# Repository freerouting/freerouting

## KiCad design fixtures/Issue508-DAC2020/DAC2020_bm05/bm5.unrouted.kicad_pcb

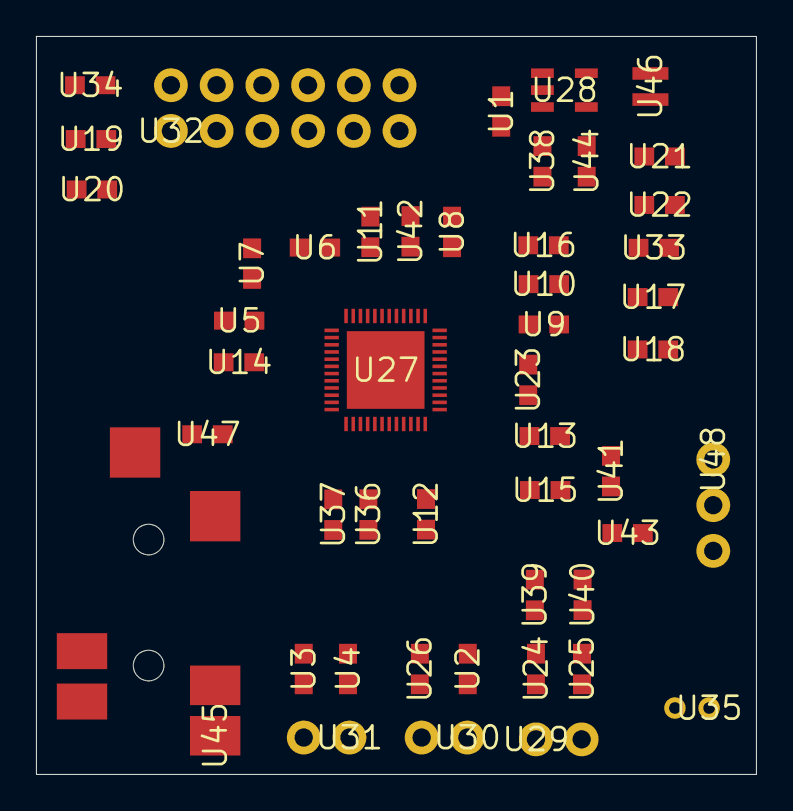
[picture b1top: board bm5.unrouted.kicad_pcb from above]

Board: 2 copper layers, 40.0 x 41.0 mm, 48 parts (0 on the bottom side), 47 nets, no tracks yet.

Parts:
U1, U2, U3, U4, U5, U6, U7, U8, U9, U10, U11, U12, U13, U14, U15, U16, U17, U18, U19, U20, U21, U22, U23, U24, U25, U26, U33, U34, U36, U37, U38, U39, U40, U41, U42, U43, U44, U47: 0603
U27: QFN50P700X700X100-49N
U28: SOT95P284X122-5N
U29, U30, U31: 1X02
U32: 2X6
U35: CMC-2242PBL-A
U45: SJ-43514-SMT-TR
U46: NRH2412T2R2MNGH
U48: 1X03

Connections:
3.3V: U32.2, U34.2
5V: U1.2, U28.1, U32.12, U33.2, U38.1
/1.8VDD: U21.1, U22.1, U27.7, U27.13, U27.21, U28.4, U46.2
/3.3VDD: U19.1, U20.1, U27.29, U34.1, U36.1, U37.1, U48.1
/CPVREF: U27.17, U42.1
/HPOL: U27.18, U45.2, U47.1
/HPOR: U27.19, U45.3
/IN1P: U23.1, U27.4, U41.2, U45.1
/IN2P: U16.1, U35.2, U43.2, U48.3
/LOUTL: U27.11, U39.1
/LOUTR: U27.12, U40.1
/MICBIAS1: U15.2, U27.2, U41.1, U43.1
/SPKVDD: U17.1, U18.1, U27.44, U27.48, U33.1
/SPOLN: U26.1, U27.47, U30.2
/SPOLP: U2.1, U27.1, U30.1
/SPORN: U3.1, U27.43, U31.2
/SPORP: U4.1, U27.45, U31.1
/XADUIO_I2S0_BCLK: U27.37, U32.5
/XADUIO_I2S0_LRCKL: U27.36, U32.1
/XADUIO_SCL: U27.39, U32.7, U37.2
/XAUDIO_I2S0_DIN: U27.35, U32.4
/XAUDIO_I2S0_DOUT: U27.34, U32.3
/XAUDIO_I2S0_MCLK: U27.38, U32.6
/XAUDIO_IRQ: U27.41, U32.10
/XAUDIO_SDA: U27.40, U32.8, U36.2
GND: U1.1, U2.2, U3.2, U4.2, U5.2, U8.1, U9.1, U10.1, U11.2, U12.1, U13.1, U14.1, U15.1, U17.2, U18.2, U19.2, U20.2, U21.2, U22.2, U26.2, U27.5, U27.15, U27.16, U27.22, U27.49, U28.2, U32.11, U35.1, U42.2, U44.1, U45.4, U48.2
unnamed: U11.1, U27.20
unnamed: U23.2, U27.6
unnamed: U24.1, U39.2
unnamed: U24.2, U29.1
unnamed: U25.1, U40.2
unnamed: U25.2, U29.2
unnamed: U5.1, U27.27
unnamed: U6.1, U27.24
unnamed: U6.2, U27.23
unnamed: U7.1, U27.25
unnamed: U7.2, U27.26
unnamed: U8.2, U27.14
unnamed: U9.2, U27.8
unnamed: U10.2, U27.9
unnamed: U12.2, U27.46
unnamed: U13.2, U27.3
unnamed: U14.2, U27.28
unnamed: U16.2, U27.10
unnamed: U28.3, U38.2, U44.2
unnamed: U28.5, U46.1
unnamed: U45.5, U47.2

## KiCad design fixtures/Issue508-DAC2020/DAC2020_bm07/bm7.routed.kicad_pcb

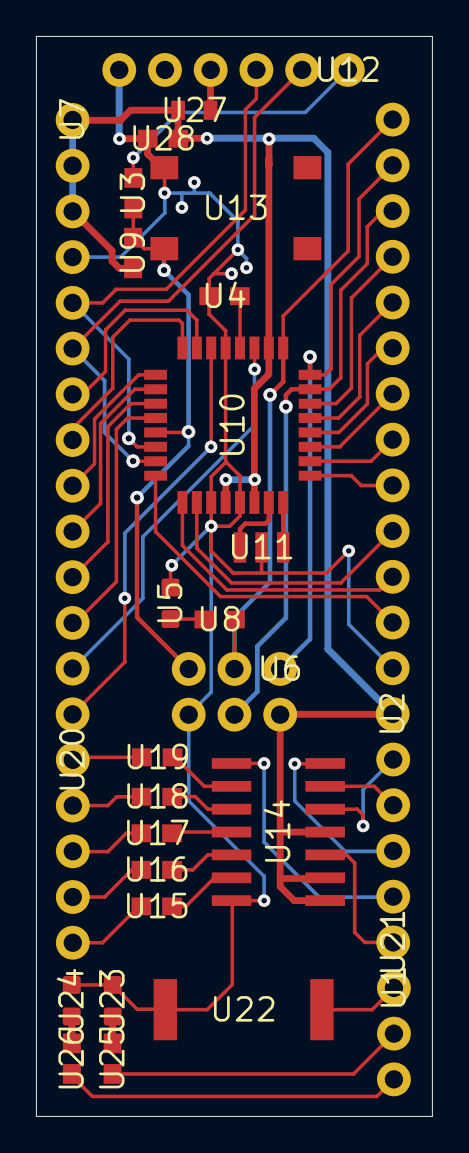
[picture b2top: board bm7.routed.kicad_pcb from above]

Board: 2 copper layers, 22.0 x 60.0 mm, 28 parts (0 on the bottom side), 51 nets.

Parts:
U1: 1X03
U2, U7: 1X14
U3, U4, U8, U9, U15, U16, U17, U18, U19, U25, U26, U28: 0603
U5, U23, U24: LED-0603
U6: 2X3
U10: TQFP32-08
U11: RESONATOR-SMD
U12: FTDI_BASIC
U13: TACTILE_SWITCH_SMD_6.2MM_TALL
U14: SO14
U20, U21: 1X05
U22: PKMCS
U27: FUSC1608X100N

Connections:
/A0: U7.7, U10.23
/A1: U7.8, U10.24
/A2: U7.9, U10.25
/A3: U7.10, U10.26
/A4: U7.11, U10.27
/A5: U7.12, U10.28
/A6: U7.13, U10.19
/A7: U7.14, U10.22
/D2: U2.3, U10.32
/D3: U2.4, U10.1
/D4: U2.5, U10.2
/D5: U2.6, U10.9
/D6: U2.7, U10.10
/D7: U2.8, U10.11
/D8: U2.9, U10.12
/D9: U2.10, U10.13
/D10: U2.11, U10.14
/DTR: U3.1, U12.DTR
/GO: U14.3, U21.1
/MISO: U2.13, U6.1, U10.16
/MOSI: U2.12, U6.4, U10.15
/OUT1: U14.8, U21.2
/OUT2: U14.7, U21.3
/OUT3: U14.6, U21.4
/OUT4: U14.5, U21.5
/RST: U3.2, U6.5, U9.1, U10.29, U13.B2
/RXI: U7.5, U10.30, U12.TXO
/SCK: U2.14, U6.3, U8.1, U10.17
/TXO: U7.6, U10.31, U12.RXI
GND: U2.2, U4.2, U5.C, U6.6, U7.4, U10.3, U10.5, U10.21, U11.2, U12.GND, U13.A2, U14.14, U22.1, U23.C, U24.C, U28.2
unnamed: U4.1, U10.20
unnamed: U5.A, U8.2
unnamed: U23.A, U25.1
unnamed: U24.A, U26.1
unnamed: U12.VCC, U27.1
unnamed: U14.9, U19.2
unnamed: U14.10, U18.2
unnamed: U14.11, U17.2
unnamed: U14.12, U16.2
unnamed: U14.13, U15.2
unnamed: U19.1, U20.1
unnamed: U18.1, U20.2
unnamed: U17.1, U20.3
unnamed: U16.1, U20.4
unnamed: U15.1, U20.5
unnamed: U1.1, U22.2
unnamed: U1.2, U25.2
unnamed: U1.3, U26.2
unnamed: U10.7, U11.3
unnamed: U10.8, U11.1
VCC: U2.1, U6.2, U7.1, U7.2, U7.3, U9.2, U10.4, U10.6, U10.18, U14.1, U14.2, U14.4, U27.2, U28.1

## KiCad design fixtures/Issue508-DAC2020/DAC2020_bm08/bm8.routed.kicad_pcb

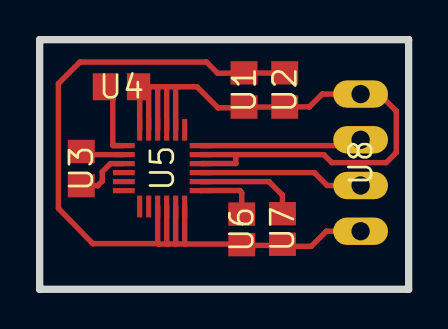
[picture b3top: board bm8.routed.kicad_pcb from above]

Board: 2 copper layers, 20.5 x 13.9 mm, 8 parts (0 on the bottom side), 9 nets.

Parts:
U1, U2, U3, U4: C0805
U5: LGA-24
U6, U7: R0805
U8: MA04-1

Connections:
/SCL: U5.21, U8.2
/SDA: U5.24, U8.3
GND: U1.2, U2.2, U4.1, U5.2, U5.3, U5.4, U5.5, U5.6, U5.22, U5.23, U8.4
unnamed: U3.1, U5.9
unnamed: U3.2, U5.8
unnamed: U4.2, U5.7
unnamed: U5.19, U6.1
unnamed: U5.20, U7.1
VDD: U1.1, U2.1, U5.15, U5.16, U5.17, U5.18, U6.2, U7.2, U8.1

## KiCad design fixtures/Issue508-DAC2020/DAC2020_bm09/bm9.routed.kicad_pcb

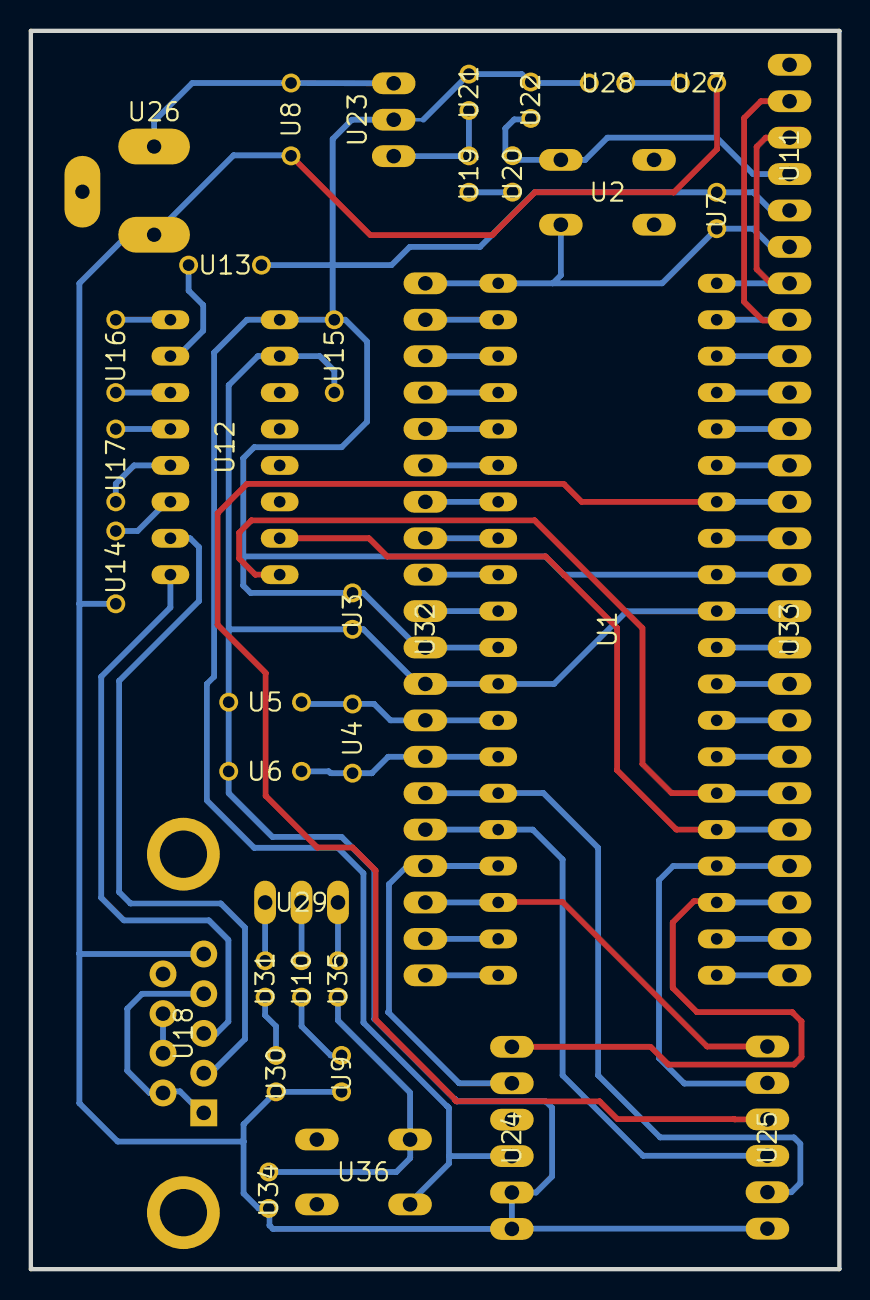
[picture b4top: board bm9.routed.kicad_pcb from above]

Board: 16 copper layers, 56.4 x 86.4 mm, 36 parts (0 on the bottom side), 58 nets.

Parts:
U1: DIL40
U2, U36: B3F-10XX
U3, U22: C025-024X044
U4: HC49_S
U5, U6, U13, U14, U15, U16, U17: C050-024X044
U7, U10, U19, U20, U21, U28, U31, U34, U35: V526-0
U8: C050-025X075
U9, U27, U30: LED3MM
U11, U24, U25: 1X06
U12: DIL16
U18: DB9
U23: 317TS
U26: 733980-62
U29: MA03-1
U32, U33: MA20-1

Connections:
/3.3V_SRC: U1.11, U1.32, U3.1, U7.1, U11.2, U12.16, U13.2, U15.1, U21.2, U22.1, U23.2, U24.3, U28.1, U32.10, U33.9, U36.1
/MRF_CS: U1.17, U24.5, U32.4
/MRF_INT: U1.34, U25.3, U33.7
/MRF_RESET: U1.15, U25.5, U32.6
/MRF_SCK: U1.18, U25.1, U32.3
/MRF_SDI: U1.23, U24.6, U33.18
/MRF_SDO: U1.24, U25.2, U33.17
/MRF_WAKE: U1.16, U25.4, U32.5
/N$17: U1.26, U12.9, U33.15
/N$21: U1.25, U12.10, U33.16
/OS1: U1.13, U4.1, U5.1, U32.8
/OSC2: U1.14, U4.2, U6.1, U32.7
GND: U1.12, U1.31, U2.1, U3.2, U5.2, U6.2, U8.2, U9.K, U11.3, U12.15, U14.1, U15.2, U18.5, U20.1, U22.2, U24.1, U24.2, U25.6, U26.1, U27.K, U30.K, U32.9, U33.10, U34.2
unnamed: U12.2, U13.1
unnamed: U12.6, U14.2
unnamed: U12.1, U16.1
unnamed: U12.3, U16.2
unnamed: U12.4, U17.1
unnamed: U12.5, U17.2
unnamed: U8.1, U23.3, U26.2
unnamed: U12.7, U18.2
unnamed: U12.8, U18.3
unnamed: U1.1, U2.3, U7.2, U11.1, U32.20
unnamed: U1.2, U32.19
unnamed: U1.3, U32.18
unnamed: U1.4, U32.17
unnamed: U1.5, U32.16
unnamed: U1.6, U32.15
unnamed: U1.7, U32.14
unnamed: U1.8, U32.13
unnamed: U1.9, U32.12
unnamed: U1.10, U32.11
unnamed: U1.19, U32.2
unnamed: U1.20, U32.1
unnamed: U1.21, U33.20
unnamed: U1.22, U33.19
unnamed: U1.27, U33.14
unnamed: U1.28, U33.13
unnamed: U1.29, U33.12
unnamed: U1.30, U33.11
unnamed: U1.33, U33.8
unnamed: U1.35, U33.6
unnamed: U1.36, U33.5
unnamed: U1.37, U33.4
unnamed: U1.38, U33.3
unnamed: U1.39, U11.5, U33.2
unnamed: U1.40, U11.4, U33.1
unnamed: U19.2, U21.1, U23.1
unnamed: U27.A, U28.2
unnamed: U30.A, U31.2
unnamed: U9.A, U10.2
unnamed: U34.1, U35.2, U36.3
unnamed: U29.3, U35.1
unnamed: U10.1, U29.2
unnamed: U29.1, U31.1
unnamed: U19.1, U20.2
unnamed: U18.1, U18.4, U18.6
unnamed: U18.7, U18.8

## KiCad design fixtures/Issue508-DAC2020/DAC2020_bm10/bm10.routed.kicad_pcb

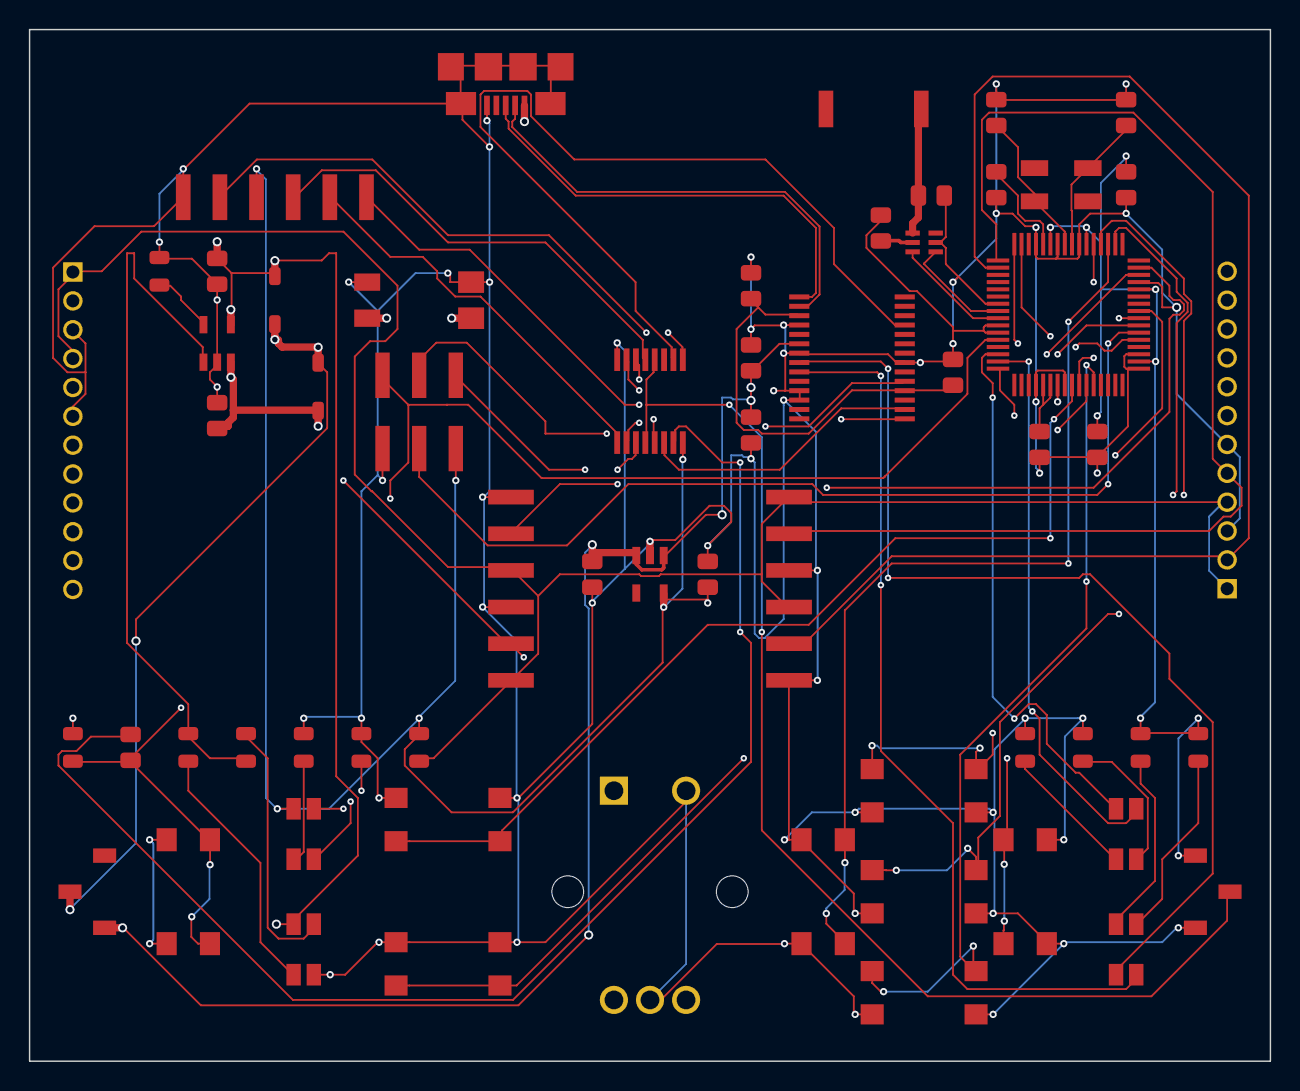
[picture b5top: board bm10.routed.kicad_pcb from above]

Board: 4 copper layers, 86.0 x 71.5 mm, 61 parts (0 on the bottom side), 63 nets.

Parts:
A1: ANTENNA-CHIP; ANT-2.4GHZ-6.5X2.2MM
B1, B4, B5, B6, B7, B8, B9, B10: PUSHBUTTON_-4.5X4.5; 4.5MM_TACTILE_SWITCH_TL3305AF160QG
B2: BALUN0805; BALUN
B3: BATTERY-SPRING-SMD; WIRE-TERMINAL-1X2-2.5MM-SMD-AVX-009276002021106
C1, C8, C9: 0.1uF; CAPC2012X140_HS
C2: 0.75pF; CAPC2012X140_HS
C3: 22pF; CAPC2012X140_HS
C4, C10, C11, C12, C13, C16, C17: 1uF; CAPC2012X140_HS
C5, C6, C7: 10uF; CAPC2012X140_HS
C14, C15: 12pF; CAPC2012X140_HS
D1, D4, D5, D6: LED-2X-GREEN_RED; LED-2X-LTST-C155
D2, D3: 360mV; SOD3716X135_HS
E1: ROTARY-ENCODER-W_BUTTON-BOURNS-PEC12R-4217F; BOURNS-PEC12R
J1: USB-MICROA-AMPHENOL-10118192-0001LF; USB-MICROA-10118192-0001LF
J2, J3: 2.4K; JST-13-PTH
J4: AVR_SPI_PRG_6-SMD; 2X3-SMD
J7, J8: FRSKY-GIMBAL-2X-SERVO-SMD; 2X-SERVO-SMD
JP1: FTDI_BASIC-SMD; FTDI-BASIC-SMD
R1, R3, R13, R14, R15, R16, R17, R18: 510; RESC2012X60_HS
R2: 10K; RESC2012X60_HS
R7: 2.2K; RESC2012X60_HS
R8: 1.2K; RESC2012X60_HS
S1, S2: POWER-SWITCH-MFS201N-9-Z-SMD-VERTICAL; JS102011JCQN
U1: 3.3V; SOT23-DBV
U2: MCP73831T-2ACI/OT; SOT23-5
U3: FT232RLSSOP; SSOP28DB
U4: ATMEGA128RFA1; QFN-64
U5: DPDT-X2; SOP65P640X110-16
Y1: CRYSTAL5X3; CRYSTAL-SMD-5X3

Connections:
3V3: C12.1, C16.1, C17.1, D4.A2, J4.2, JP1.VCC, R2.2, R8.2, R13.2, R14.2, S2.1, U1.5, U4.23, U4.34, U4.44, U4.54, U4.59, U5.16
/BTN1/SCL: B4.3, B4.4, U4.25
/BTN2/SDA: B5.3, B5.4, U4.26
/BTN_CENTER: B9.1, B9.2, U4.53
/BTN_DOWN: B10.1, B10.2, U4.28
/BTN_LEFT: B7.1, B7.2, U4.51
/BTN_RIGHT: B8.1, B8.2, U4.52
/BTN_UP: B6.1, B6.2, U4.50
/CTS: U3.11, U5.2
/CTS-1: JP1.CTS, U5.1
/DTR: U3.2, U5.14
/DTR-0: C1.2, U5.15
/DTR-1: JP1.DTR, U5.13
/E1-A: E1.A, U4.40
/E1-B: E1.B, U4.41
/E1-BUT: E1.BUTA, U4.27
/FTDI_OUT: C4.2, C9.1, U3.4, U3.17
/GREF: J2.1, J2.4, J3.1, J3.4, J7.1, J7.4, J8.1, J8.4, R8.1
/MISO: J4.1, U4.39
/MOSI: J4.4, U4.38
/PITCH: J3.V, J8.V, U4.2
/RESET: B1.1, B1.2, C1.1, J4.5, R2.1, U4.12
/RF: D4.A1, U4.16
/ROLL: J3.H, J8.H, U4.1
/RXI: U3.5, U5.10
/RXI-0: U4.47, U5.11
/RXI-1: JP1.RXI, U5.9
/RXLED: D5.C2, U3.22
/SCK: J4.3, U4.37
/THROTTLE: J2.V, J7.V, U4.64
/TXLED: D5.C1, U3.23
/TXO: U3.1, U5.6
/TXO-0: U4.46, U5.7
/TXO-1: JP1.TXO, U5.5
/USB_D_N: J1.2, U3.16
/USB_D_P: J1.3, U3.15
/VBUS: C5.1, D1.A2, D2.A, J1.1, U2.4
/VREG_IN: C7.1, C8.1, C10.1, S1.1, U1.1, U1.3, U3.20
/YAW: J2.H, J7.H, U4.63
GND: B1.3, B1.4, B2.5, B3.2A, B3.2B, B4.1, B4.2, B5.1, B5.2, B6.3, B6.4, B7.3, B7.4, B8.3, B8.4, B9.3, B9.4, B10.3, B10.4, C2.2, C3.1, C4.1, C5.2, C6.2, C7.2, C8.2, C9.2, C10.2, C11.2, C12.2, C13.2, C14.2, C15.2, C16.2, C17.2, D1.C1, E1.BUTB, E1.C, J1.5, J1.6, J1.7, J1.8, J1.9, J1.10, J1.11, J2.3, J2.6, J3.3, J3.6, J4.6, J7.3, J7.6, J8.3, J8.6, JP1.GND, R7.2, R15.1, R16.1, R17.1, R18.1, S2.3, U1.2, U2.2, U3.7, U3.18, U3.21, U3.25, U3.26, U4.7, U4.10, U4.11, U4.20, U4.24, U4.33, U4.35, U4.45, U4.55, U4.58, U4.61, U5.8
unnamed: A1.FEED, B2.1, C2.1
unnamed: B2.2, C3.2
unnamed: B2.3, U4.9
unnamed: B2.4, U4.8
unnamed: B3.1A, B3.1B, C6.1, D3.A, U2.3
unnamed: C11.1, U4.21, U4.22
unnamed: C13.1, U4.60
unnamed: C14.1, U4.57, Y1.3
unnamed: C15.1, U4.56, Y1.1
unnamed: D1.A1, R3.1
unnamed: D1.C2, R1.1
unnamed: D4.C1, R15.2
unnamed: D4.C2, R16.2
unnamed: D5.A1, R14.1
unnamed: D5.A2, R13.1
unnamed: D6.A1, U4.15
unnamed: D6.A2, U4.14
unnamed: D6.C1, R18.2
unnamed: D6.C2, R17.2
unnamed: R1.2, R3.2, U2.1
unnamed: R7.1, U2.5
unnamed: S2.2, U5.4, U5.12
VBAT: D2.C, D3.C, S1.2

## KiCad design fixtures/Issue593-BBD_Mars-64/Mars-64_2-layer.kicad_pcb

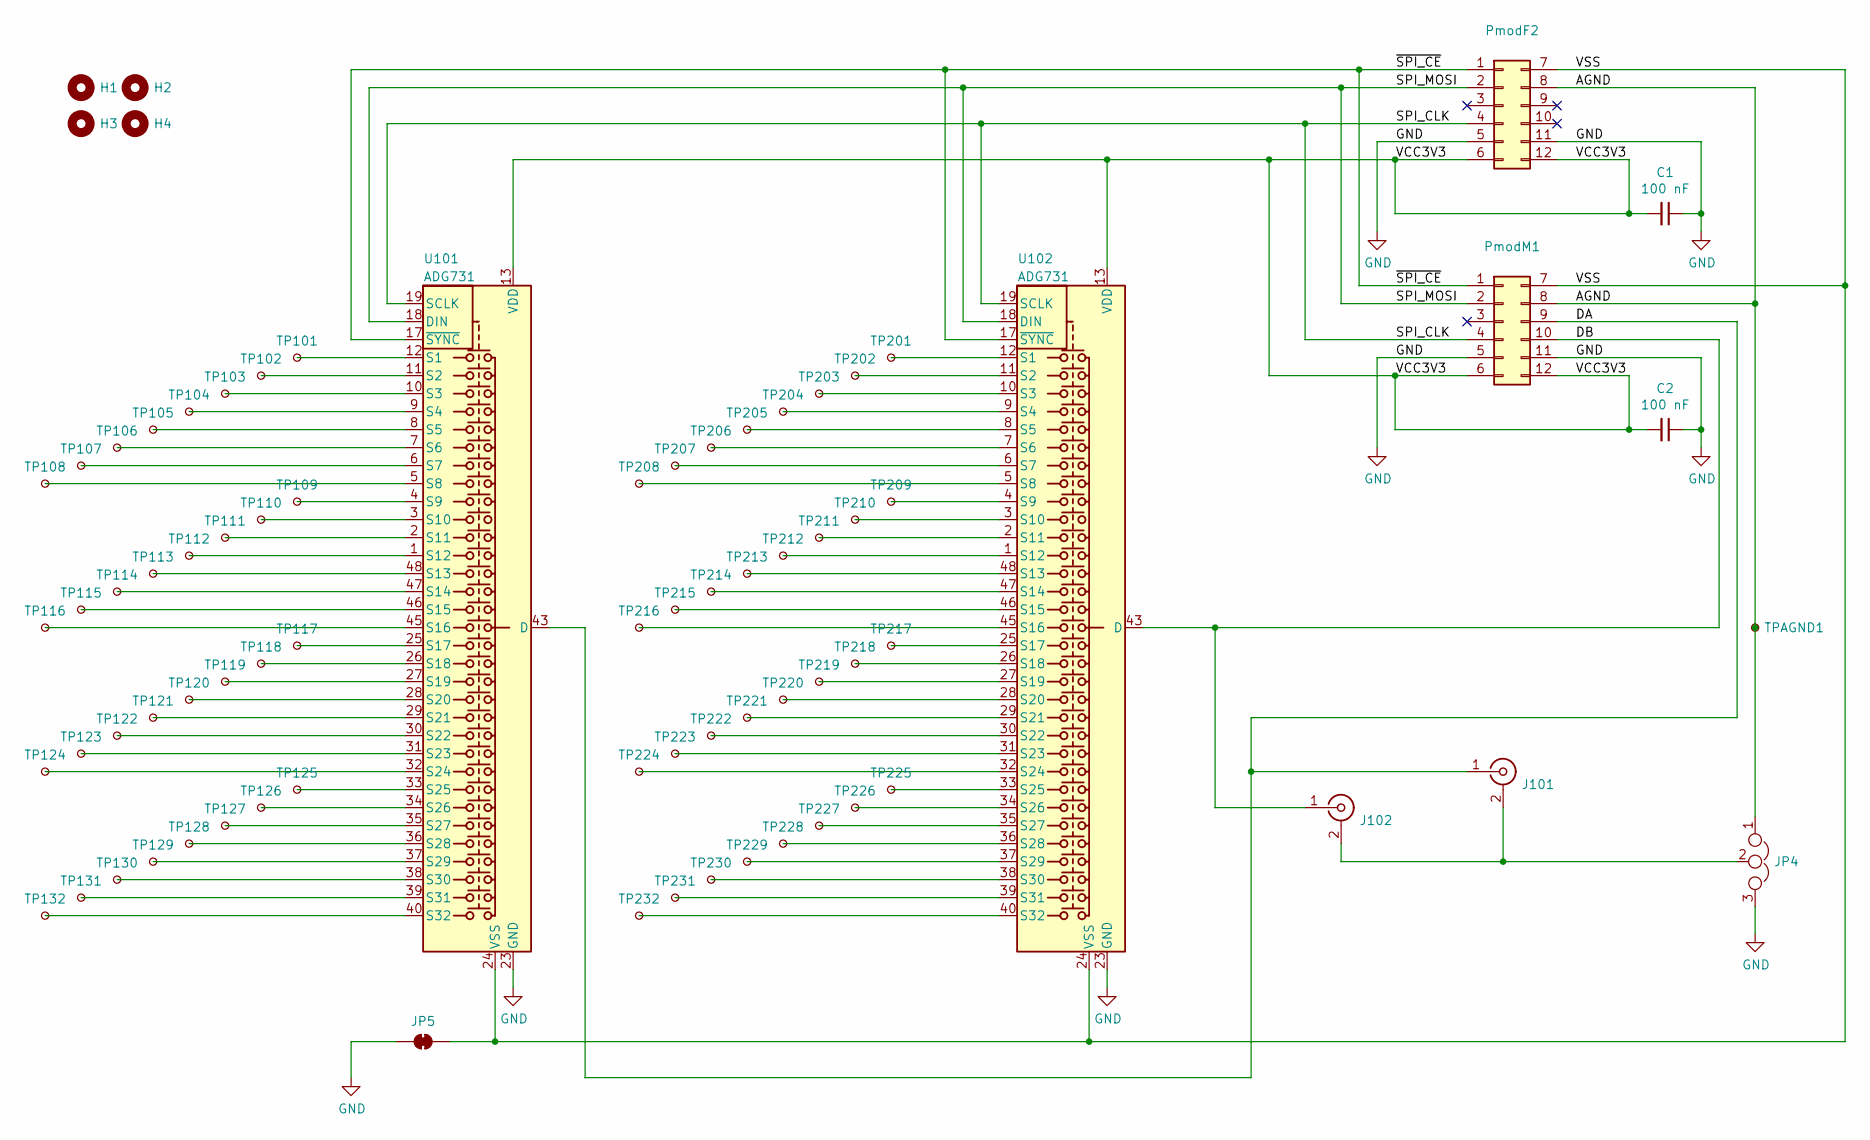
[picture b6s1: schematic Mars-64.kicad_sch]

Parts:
C1, C2: 100 nF; C_1206_3216Metric_Pad1.42x1.75mm_HandSolder
H1, H2, H3, H4: MountingHole; MountingHole_2.7mm_M2.5
J101, J102: Conn_Coaxial; SMA_Amphenol_132134-10_Vertical
JP4: Jumper_NC_Dual; SolderJumper-3_P1.3mm_Bridged2Bar12_Pad1.0x1.5mm_NumberLabe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
JP5: SolderJumper_2_Bridged; SolderJumper-2_P1.3mm_Bridged_RoundedPad1.0x1.5mm
PmodF2: Conn_02x06_Top_Bottom; PinHeader_2x06_P2.54mm_Vertical_SMD_TopBottom
PmodM1: Conn_02x06_Top_Bottom; PinHeader_2x06_P2.54mm_Vertical_SMD_TopBottom_Mirrored
TP101, TP102, TP103, TP104, TP105, TP106, TP107, TP108, TP109, TP110, TP111, TP112, TP113, TP114, TP115, TP116, TP117, TP118, TP119, TP120, TP121, TP122, TP123, TP124, TP125, TP126, TP127, TP128, TP129, TP130, TP131, TP132, TP201, TP202, TP203, TP204, TP205, TP206, TP207, TP208, TP209, TP210, TP211, TP212, TP213, TP214, TP215, TP216, TP217, TP218, TP219, TP220, TP221, TP222, TP223, TP224, TP225, TP226, TP227, TP228, TP229, TP230, TP231, TP232: TestPoint_Small; TestPoint_Pad_4.0x4.0mm
TPAGND1: TestPoint_Small; TestPoint_Pad_1.0x1.0mm
U101, U102: ADG731; TQFP-48_7x7mm_P0.5mm

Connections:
/AGND: JP4.1, PmodF2.8, PmodM1.8, TPAGND1.1; also elsewhere on the board
/DA: J101.1 (In), PmodM1.9, U101.43 (D); also elsewhere on the board
/DB: J102.1 (In), PmodM1.10, U102.43 (D); also elsewhere on the board
/SPI_CLK: PmodF2.4, PmodM1.4, U101.19 (SCLK), U102.19 (SCLK); also elsewhere on the board
/SPI_MOSI: PmodF2.2, PmodM1.2, U101.18 (DIN), U102.18 (DIN); also elsewhere on the board
/VCC3V3: C1.2, C2.2, PmodF2.6, PmodF2.12, PmodM1.6, PmodM1.12, U101.13 (VDD), U101.14 (VDD), U102.13 (VDD), U102.14 (VDD); also elsewhere on the board
/VSS: JP5.2 (B), PmodF2.7, PmodM1.7, U101.24 (VSS), U102.24 (VSS); also elsewhere on the board
/~SPI_CE: PmodF2.1, PmodM1.1, U101.17 (~SYNC), U102.17 (~SYNC); also elsewhere on the board
GND: C1.1, C2.1, JP4.3, JP5.1 (A), PmodF2.5, PmodF2.11, PmodM1.5, PmodM1.11, U101.23 (GND), U102.23 (GND); also elsewhere on the board
unnamed 9: J101.2 (Ext), J102.2 (Ext), JP4.2; also elsewhere on the board
unnamed: TP101.1, U101.12 (S1)
unnamed: TP102.1, U101.11 (S2)
unnamed: TP103.1, U101.10 (S3)
unnamed: TP104.1, U101.9 (S4)
unnamed: TP105.1, U101.8 (S5)
unnamed: TP106.1, U101.7 (S6)
unnamed: TP107.1, U101.6 (S7)
unnamed: TP108.1, U101.5 (S8)
unnamed: TP109.1, U101.4 (S9)
unnamed: TP110.1, U101.3 (S10)
unnamed: TP111.1, U101.2 (S11)
unnamed: TP112.1, U101.1 (S12)
unnamed: TP113.1, U101.48 (S13)
unnamed: TP114.1, U101.47 (S14)
unnamed: TP115.1, U101.46 (S15)
unnamed: TP116.1, U101.45 (S16)
unnamed: TP117.1, U101.25 (S17)
unnamed: TP118.1, U101.26 (S18)
unnamed: TP119.1, U101.27 (S19)
unnamed: TP120.1, U101.28 (S20)
unnamed: TP121.1, U101.29 (S21)
unnamed: TP122.1, U101.30 (S22)
unnamed: TP123.1, U101.31 (S23)
unnamed: TP124.1, U101.32 (S24)
unnamed: TP125.1, U101.33 (S25)
unnamed: TP126.1, U101.34 (S26)
unnamed: TP127.1, U101.35 (S27)
unnamed: TP128.1, U101.36 (S28)
unnamed: TP129.1, U101.37 (S29)
unnamed: TP130.1, U101.38 (S30)
unnamed: TP131.1, U101.39 (S31)
unnamed: TP132.1, U101.40 (S32)
unnamed: TP201.1, U102.12 (S1)
unnamed: TP202.1, U102.11 (S2)
unnamed: TP203.1, U102.10 (S3)
unnamed: TP204.1, U102.9 (S4)
unnamed: TP205.1, U102.8 (S5)
unnamed: TP206.1, U102.7 (S6)
unnamed: TP207.1, U102.6 (S7)
unnamed: TP208.1, U102.5 (S8)
unnamed: TP209.1, U102.4 (S9)
unnamed: TP210.1, U102.3 (S10)
unnamed: TP211.1, U102.2 (S11)
unnamed: TP212.1, U102.1 (S12)
unnamed: TP213.1, U102.48 (S13)
unnamed: TP214.1, U102.47 (S14)
unnamed: TP215.1, U102.46 (S15)
unnamed: TP216.1, U102.45 (S16)
unnamed: TP217.1, U102.25 (S17)
unnamed: TP218.1, U102.26 (S18)
unnamed: TP219.1, U102.27 (S19)
unnamed: TP220.1, U102.28 (S20)
unnamed: TP221.1, U102.29 (S21)
unnamed: TP222.1, U102.30 (S22)
unnamed: TP223.1, U102.31 (S23)
unnamed: TP224.1, U102.32 (S24)
unnamed: TP225.1, U102.33 (S25)
unnamed: TP226.1, U102.34 (S26)
unnamed: TP227.1, U102.35 (S27)
unnamed: TP228.1, U102.36 (S28)
unnamed: TP229.1, U102.37 (S29)
unnamed: TP230.1, U102.38 (S30)
unnamed: TP231.1, U102.39 (S31)
unnamed: TP232.1, U102.40 (S32)

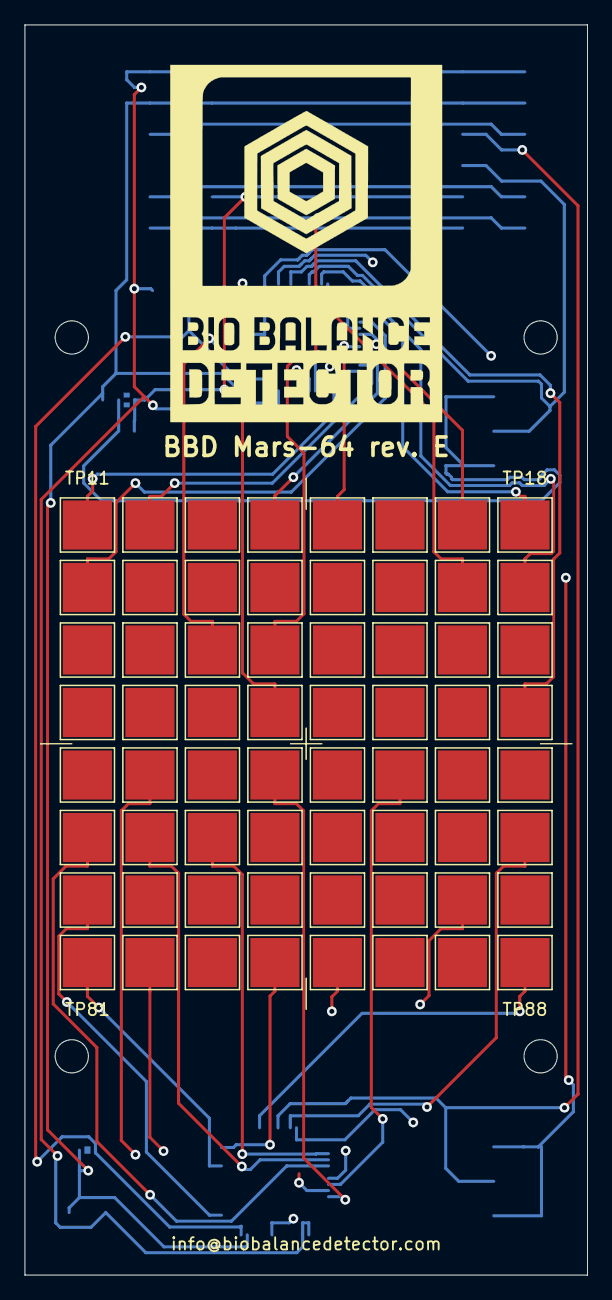
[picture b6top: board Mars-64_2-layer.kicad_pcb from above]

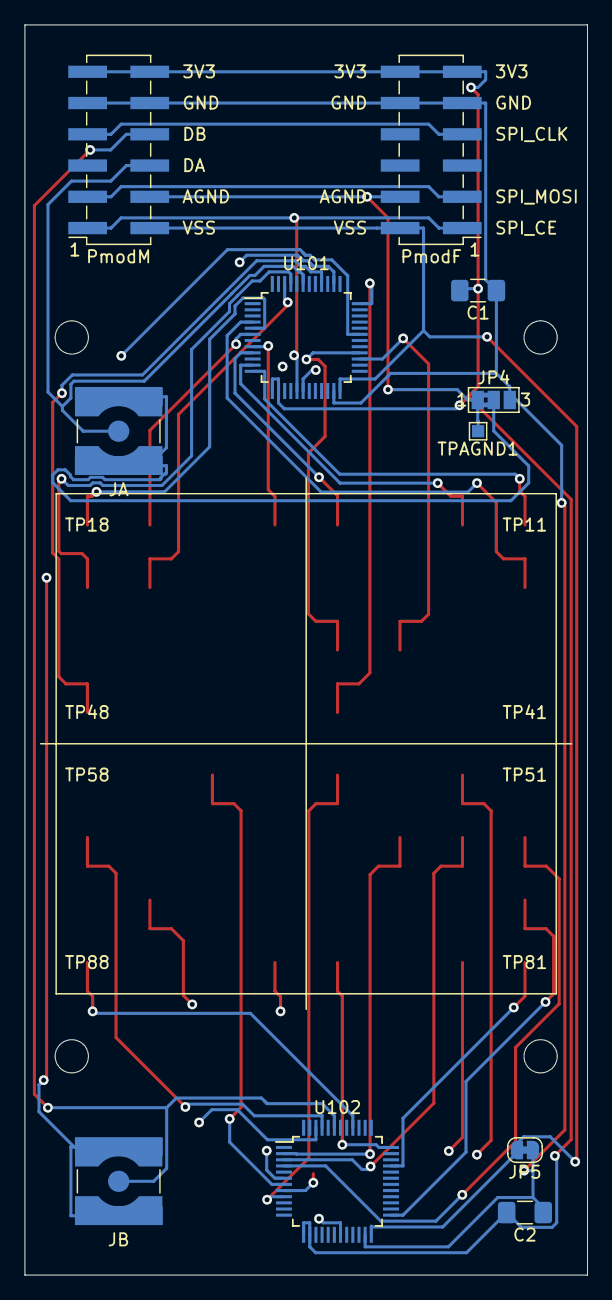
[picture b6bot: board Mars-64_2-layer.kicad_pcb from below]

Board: 2 copper layers, 45.7 x 101.6 mm, 79 parts (11 on the bottom side), 74 nets.

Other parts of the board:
JA: Conn_Coaxial; SMA_Amphenol_132134-10_Vertical
JB: Conn_Coaxial; SMA_Amphenol_132134-10_Vertical
PmodF: Conn_02x06_Top_Bottom; PinHeader_2x06_P2.54mm_Vertical_SMD_TopBottom
PmodM: Conn_02x06_Top_Bottom; PinHeader_2x06_P2.54mm_Vertical_SMD_TopBottom_Mirrored

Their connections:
/AGND: PmodF.8, PmodM.8; also elsewhere on the board
/DA: JA.1, PmodM.9; also elsewhere on the board
/DB: JB.1, PmodM.10; also elsewhere on the board
/SPI_CLK: PmodF.4, PmodM.4; also elsewhere on the board
/SPI_MOSI: PmodF.2, PmodM.2; also elsewhere on the board
/VCC3V3: PmodF.6, PmodF.12, PmodM.6, PmodM.12; also elsewhere on the board
/VSS: PmodF.7, PmodM.7; also elsewhere on the board
/~SPI_CE: PmodF.1, PmodM.1; also elsewhere on the board
GND: PmodF.5, PmodF.11, PmodM.5, PmodM.11; also elsewhere on the board
unnamed 9: JA.2, JB.2; also elsewhere on the board

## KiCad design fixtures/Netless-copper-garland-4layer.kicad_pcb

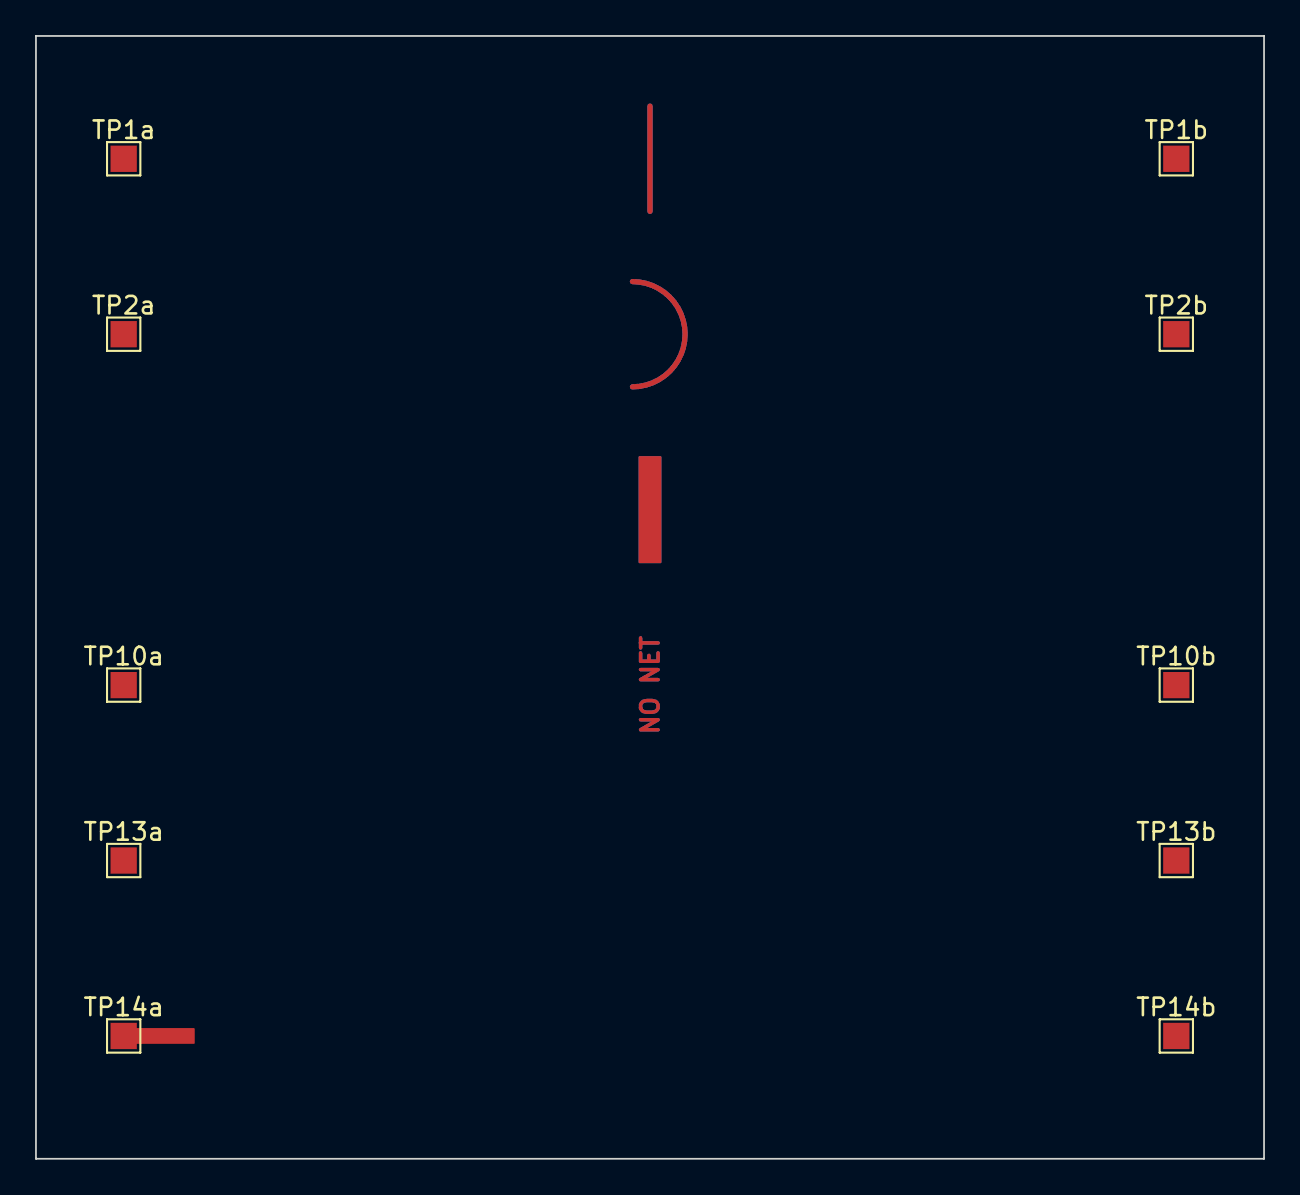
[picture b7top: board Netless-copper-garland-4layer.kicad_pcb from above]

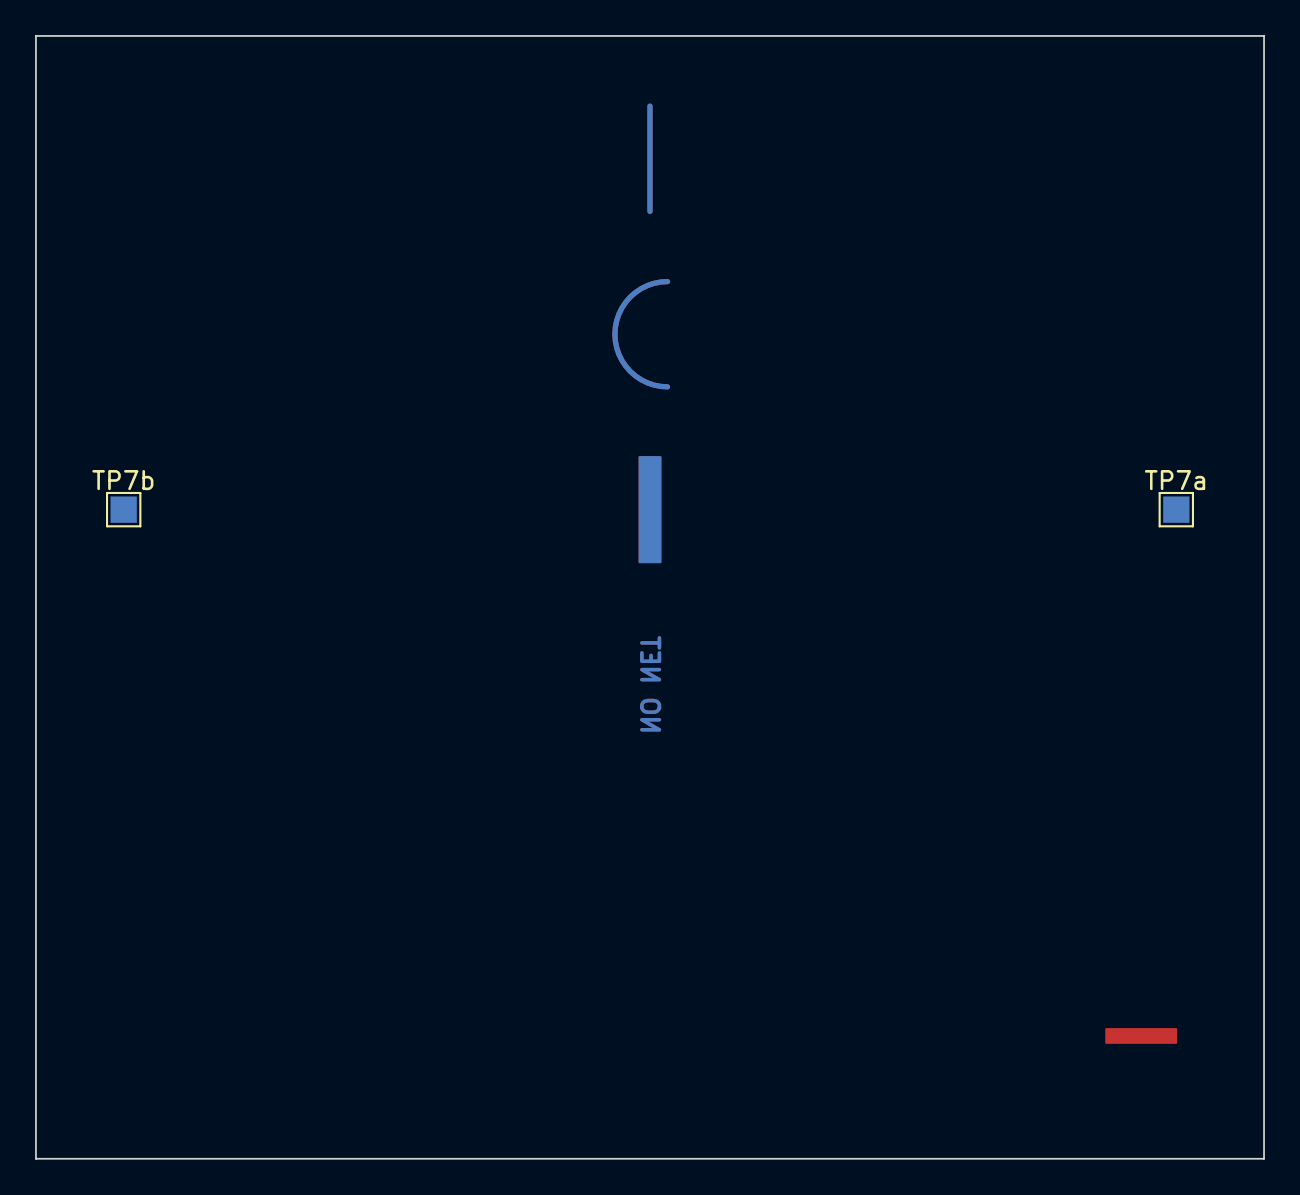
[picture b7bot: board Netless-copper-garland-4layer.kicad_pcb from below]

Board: 4 copper layers, 70.0 x 64.0 mm, 14 parts (2 on the bottom side), 6 nets, no tracks yet.

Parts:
NL1, NL2: (no value)
TP1a, TP1b, TP2a, TP2b, TP7a, TP7b, TP10a, TP10b, TP13a, TP13b, TP14a, TP14b: TestPoint_Pad_1.5x1.5mm

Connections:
N1: TP1a.1, TP1b.1
N2: TP2a.1, TP2b.1
N7: TP7a.1, TP7b.1
N10: TP10a.1, TP10b.1
N13: TP13a.1, TP13b.1
N14: TP14a.1, TP14b.1
